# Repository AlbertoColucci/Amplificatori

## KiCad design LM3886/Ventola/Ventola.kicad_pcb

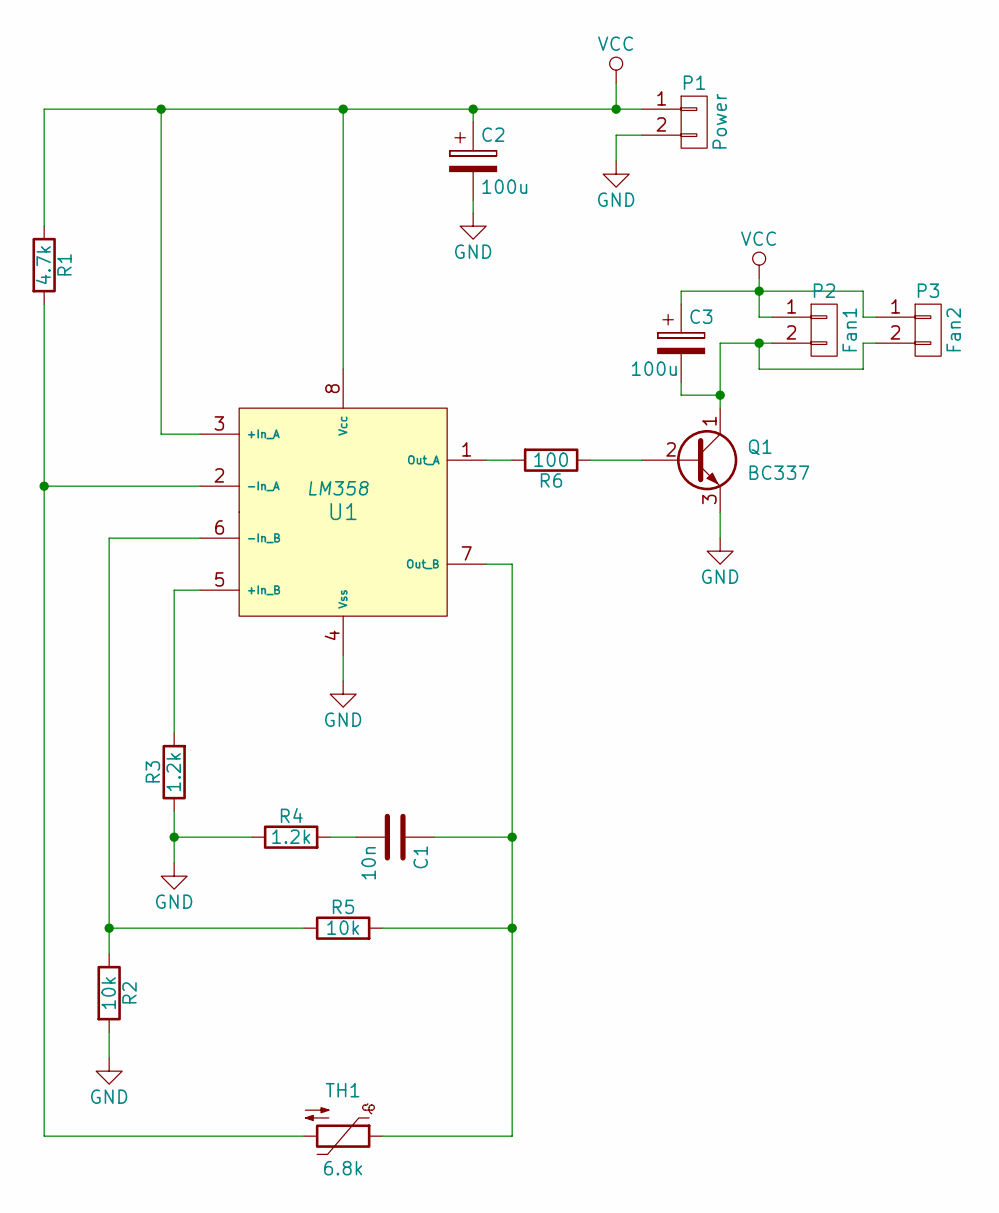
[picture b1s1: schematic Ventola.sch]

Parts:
C1: 10n; Cap_5x2.7
C2, C3: 100u; Cap_6.3
P1: Power; AK300-2
P2: Fan1; AK300-2
P3: Fan2; AK300-2
Q1: BC337; TO-92
R1: 4.7k; Res_Orizz_10mm
R2, R5: 10k; Res_Orizz_10mm
R3, R4: 1.2k; Res_Orizz_10mm
R6: 100; Res_Orizz_10mm
TH1: 6.8k; 2-Pin
U1: LM358; DIP-8

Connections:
GND: C2.2, P1.2, Q1.3 (E), R2.2, R3.1, R4.1, U1.4 (Vss)
unnamed: C1.1, R5.2, TH1.1, U1.7 (Out_B)
unnamed: C1.2, R4.2
unnamed: C3.2, P2.2, P3.2, Q1.1 (C)
unnamed: Q1.2 (B), R6.1
unnamed: R1.2, TH1.2, U1.2 (-In_A)
unnamed: R2.1, R5.1, U1.6 (-In_B)
unnamed: R3.2, U1.5 (+In_B)
unnamed: R6.2, U1.1 (Out_A)
VCC: C2.1, C3.1, P1.1, P2.1, P3.1, R1.1, U1.3 (+In_A), U1.8 (Vcc)

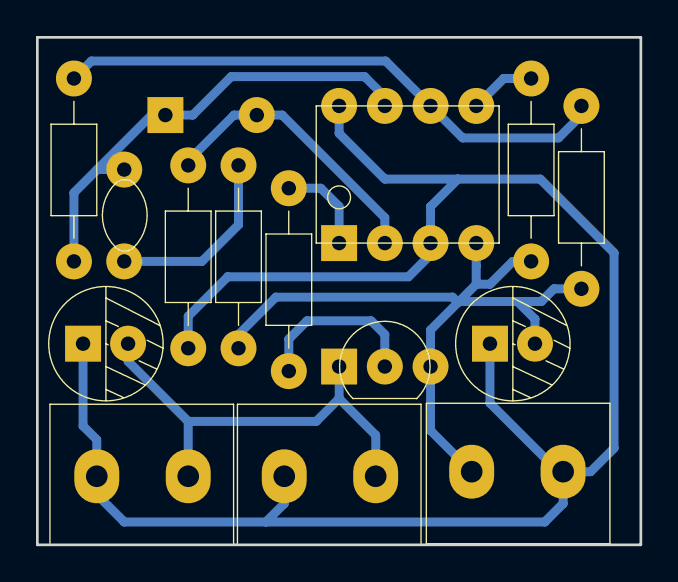
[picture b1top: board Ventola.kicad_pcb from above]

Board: 2 copper layers, 33.5 x 28.2 mm, 15 parts (0 on the bottom side), 10 nets.
